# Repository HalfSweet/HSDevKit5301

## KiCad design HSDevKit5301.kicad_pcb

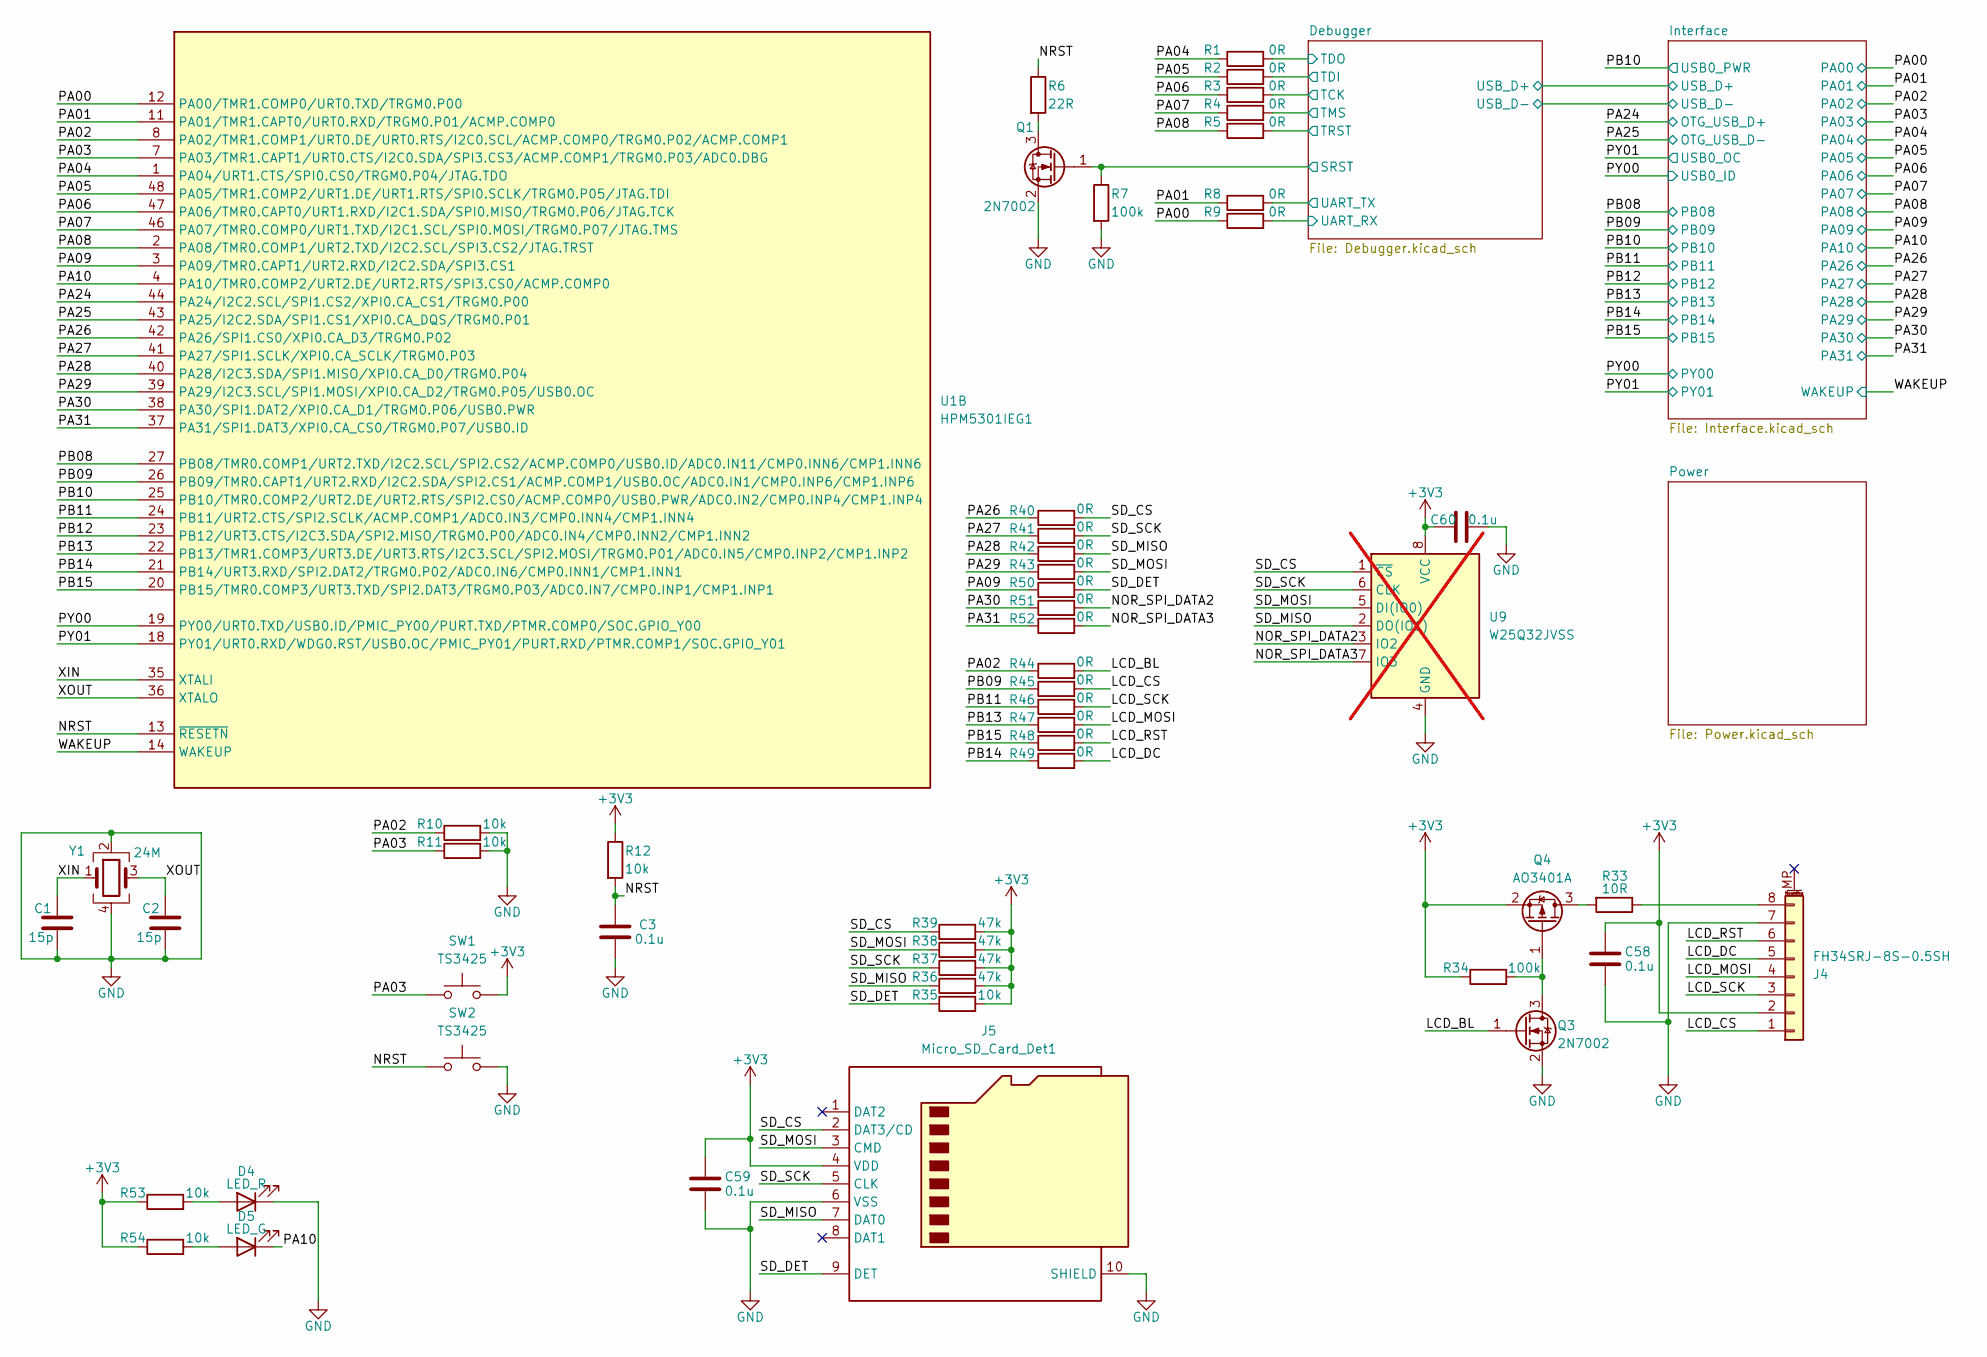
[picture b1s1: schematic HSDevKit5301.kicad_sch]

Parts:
C1, C2: 15p; C_0402_1005Metric
C3, C58, C59, C60: 0.1u; C_0402_1005Metric
D4: LED_R; LED_0402_1005Metric
D5: LED_G; LED_0402_1005Metric
J4: FH34SRJ-8S-0.5SH; FPC-SMD_8P-P0.50-FH34SRJ
J5: Micro_SD_Card_Det1; TF-SMD_TF-06A
Q1, Q3: 2N7002; SOT-323_SC-70
Q4: AO3401A; SOT-23
R1, R2, R3, R4, R5, R8, R9, R40, R41, R42, R43, R44, R45, R46, R47, R48, R49, R50, R51, R52: 0R; R_0402_1005Metric
R6: 22R; R_0402_1005Metric
R7, R34: 100k; R_0402_1005Metric
R10, R11, R12, R35, R53, R54: 10k; R_0402_1005Metric
R33: 10R; R_0603_1608Metric
R36, R37, R38, R39: 47k; R_0402_1005Metric
SW1, SW2: TS3425; SW_SPST_PTS810
U1: HPM5301IEG1; QFN-48-1EP_6x6mm_P0.4mm_EP4.2x4.2mm
U9: W25Q32JVSS; SOIC-8_5.23x5.23mm_P1.27mm; not fitted
Y1: 24M; Crystal_SMD_2016-4Pin_2.0x1.6mm

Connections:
+3V3: C58.1, C59.1, C60.1, J4.2, J5.4 (VDD), Q4.2 (S), R12.1, R34.1, R35.2, R36.2, R37.2, R38.2, R39.2, R53.1, R54.1, SW1.2, U9.8 (VCC); also elsewhere on the board
/Debugger/SRST: Q1.1 (G), R7.1; also elsewhere on the board
/Debugger/TCK: R3.2; also elsewhere on the board
/Debugger/TDI: R2.2; also elsewhere on the board
/Debugger/TDO: R1.2; also elsewhere on the board
/Debugger/TMS: R4.2; also elsewhere on the board
/Debugger/TRST: R5.2; also elsewhere on the board
/Debugger/UART_RX: R9.2; also elsewhere on the board
/Debugger/UART_TX: R8.2; also elsewhere on the board
/LCD_BL: Q3.1 (G), R44.2
/LCD_CS: J4.1, R45.2
/LCD_DC: J4.5, R49.2
/LCD_MOSI: J4.4, R47.2
/LCD_RST: J4.6, R48.2
/LCD_SCK: J4.3, R46.2
/NOR_SPI_DATA2: R51.2, U9.3 (IO2)
/NOR_SPI_DATA3: R52.2, U9.7 (IO3)
/NRST: C3.1, R6.1, R12.2, SW2.1, U1.13 (~RESETN)
/PA00: R9.1, U1.12 (PA00/TMR1.COMP0/URT0.TXD/TRGM0.P00); also elsewhere on the board
/PA01: R8.1, U1.11 (PA01/TMR1.CAPT0/URT0.RXD/TRGM0.P01/ACMP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); also elsewhere on the board
/PA02: R10.1, R44.1, U1.8 (PA02/TMR1.COMP1/URT0.DE/URT0.RTS/I2C0.S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); also elsewhere on the board
/PA03: R11.1, SW1.1, U1.7 (PA03/TMR1.CAPT1/URT0.CTS/I2C0.SDA/SPI3.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); also elsewhere on the board
/PA04: R1.1, U1.1 (PA04/URT1.CTS/SPI0.CS0/TRGM0.P04/JTAG.T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); also elsewhere on the board
/PA05: R2.1, U1.48 (PA05/TMR1.COMP2/URT1.DE/URT1.RTS/SPI0.S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); also elsewhere on the board
/PA06: R3.1, U1.47 (PA06/TMR0.CAPT0/URT1.RXD/I2C1.SDA/SPI0.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); also elsewhere on the board
/PA07: R4.1, U1.46 (PA07/TMR0.COMP0/URT1.TXD/I2C1.SCL/SPI0.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); also elsewhere on the board
/PA08: R5.1, U1.2 (PA08/TMR0.COMP1/URT2.TXD/I2C2.SCL/SPI3.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); also elsewhere on the board
/PA09: R50.1, U1.3 (PA09/TMR0.CAPT1/URT2.RXD/I2C2.SDA/SPI3.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); also elsewhere on the board
/PA10: D5.1 (K), U1.4 (PA10/TMR0.COMP2/URT2.DE/URT2.RTS/SPI3.C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); also elsewhere on the board
/PA24: U1.44 (PA24/I2C2.SCL/SPI1.CS2/XPI0.CA_CS1/TRGM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); also elsewhere on the board
/PA25: U1.43 (PA25/I2C2.SDA/SPI1.CS1/XPI0.CA_DQS/TRGM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); also elsewhere on the board
/PA26: R40.1, U1.42 (PA26/SPI1.CS0/XPI0.CA_D3/TRGM0.P02); also elsewhere on the board
/PA27: R41.1, U1.41 (PA27/SPI1.SCLK/XPI0.CA_SCLK/TRGM0.P03); also elsewhere on the board
/PA28: R42.1, U1.40 (PA28/I2C3.SDA/SPI1.MISO/XPI0.CA_D0/TRGM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); also elsewhere on the board
/PA29: R43.1, U1.39 (PA29/I2C3.SCL/SPI1.MOSI/XPI0.CA_D2/TRGM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); also elsewhere on the board
/PA30: R51.1, U1.38 (PA30/SPI1.DAT2/XPI0.CA_D1/TRGM0.P06/USB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); also elsewhere on the board
/PA31: R52.1, U1.37 (PA31/SPI1.DAT3/XPI0.CA_CS0/TRGM0.P07/US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); also elsewhere on the board
/PB08: U1.27 (PB08/TMR0.COMP1/URT2.TXD/I2C2.SCL/SPI2.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); also elsewhere on the board
/PB09: R45.1, U1.26 (PB09/TMR0.CAPT1/URT2.RXD/I2C2.SDA/SPI2.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); also elsewhere on the board
/PB10: U1.25 (PB10/TMR0.COMP2/URT2.DE/URT2.RTS/SPI2.C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); also elsewhere on the board
/PB11: R46.1, U1.24 (PB11/URT2.CTS/SPI2.SCLK/ACMP.COMP1/ADC0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); also elsewhere on the board
/PB12: U1.23 (PB12/URT3.CTS/I2C3.SDA/SPI2.MISO/TRGM0.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); also elsewhere on the board
/PB13: R47.1, U1.22 (PB13/TMR1.COMP3/URT3.DE/URT3.RTS/I2C3.S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); also elsewhere on the board
/PB14: R49.1, U1.21 (PB14/URT3.RXD/SPI2.DAT2/TRGM0.P02/ADC0.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); also elsewhere on the board
/PB15: R48.1, U1.20 (PB15/TMR0.COMP3/URT3.TXD/SPI2.DAT3/TRGM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); also elsewhere on the board
/PY00: U1.19 (PY00/URT0.TXD/USB0.ID/PMIC_PY00/PURT.TX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); also elsewhere on the board
/PY01: U1.18 (PY01/URT0.RXD/WDG0.RST/USB0.OC/PMIC_PY0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); also elsewhere on the board
/SD_CS: J5.2 (DAT3/CD), R39.1, R40.2, U9.1 (~CS)
/SD_DET: J5.9 (DET), R35.1, R50.2
/SD_MISO: J5.7 (DAT0), R36.1, R42.2, U9.2 (DO(IO1))
/SD_MOSI: J5.3 (CMD), R38.1, R43.2, U9.5 (DI(IO0))
/SD_SCK: J5.5 (CLK), R37.1, R41.2, U9.6 (CLK)
/WAKEUP: U1.14 (WAKEUP); also elsewhere on the board
/XIN: C1.1, U1.35 (XTALI), Y1.1
/XOUT: C2.1, U1.36 (XTALO), Y1.3
GND: C1.2, C2.2, C3.2, C58.2, C59.2, C60.2, D4.1 (K), J4.7, J5.6 (VSS), J5.10 (SHIELD), Q1.2 (S), Q3.2 (S), R7.2, R10.2, R11.2, SW2.2, U9.4 (GND), Y1.2, Y1.4; also elsewhere on the board
unnamed: D4.2 (A), R53.2
unnamed: D5.2 (A), R54.2
unnamed: J4.8, R33.1
unnamed: Q1.3 (D), R6.2
unnamed: Q3.3 (D), Q4.1 (G), R34.2
unnamed: Q4.3 (D), R33.2

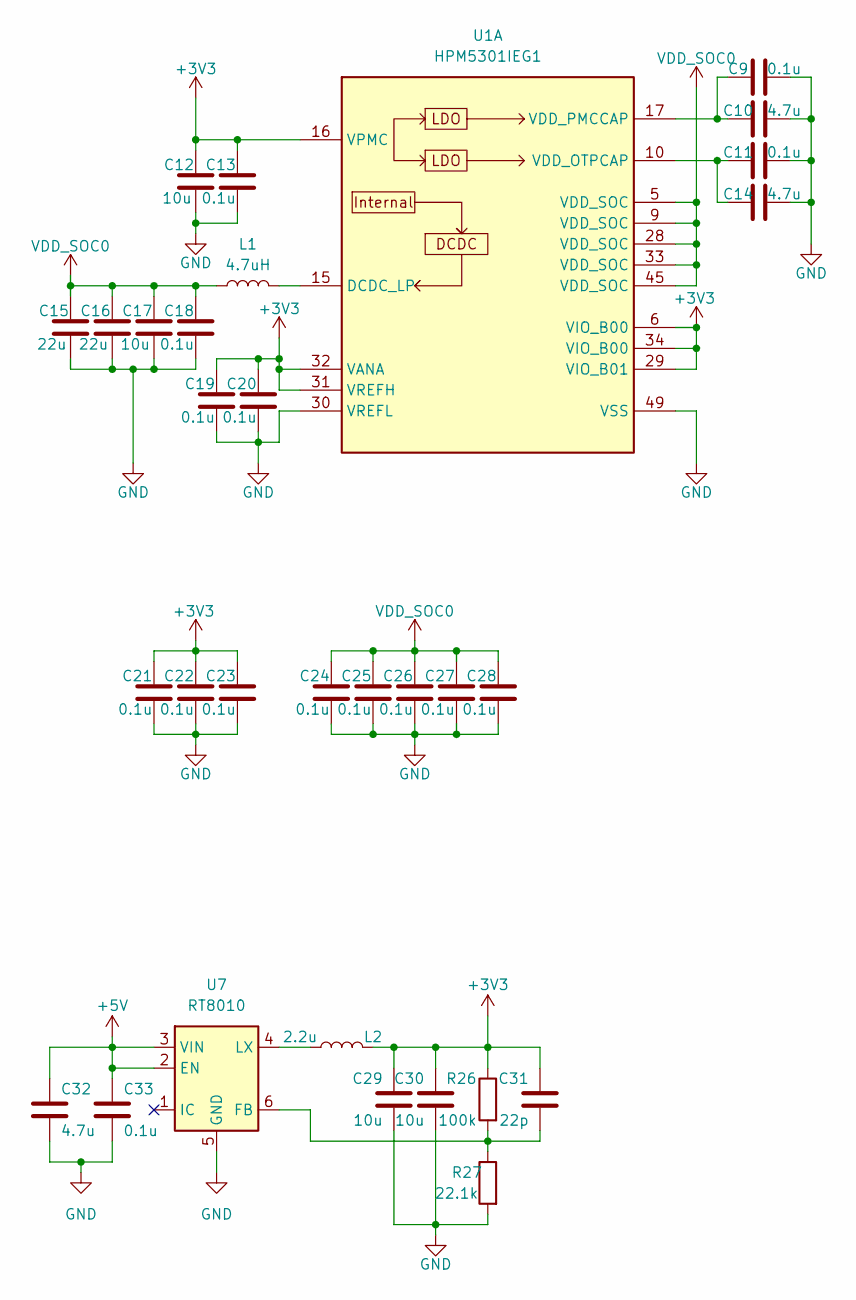
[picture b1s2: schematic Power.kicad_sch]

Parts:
C9, C11, C13, C18, C19, C20, C21, C22, C23, C24, C25, C26, C27, C28, C33: 0.1u; C_0402_1005Metric
C10, C14, C32: 4.7u; C_0402_1005Metric
C12, C17, C29, C30: 10u; C_0402_1005Metric
C15, C16: 22u; C_0402_1005Metric
C31: 22p; C_0402_1005Metric
L1: 4.7uH; L_1008_2520Metric
L2: 2.2u; L_1008_2520Metric
R26: 100k; R_0402_1005Metric
R27: 22.1k; R_0402_1005Metric
U1: HPM5301IEG1; QFN-48-1EP_6x6mm_P0.4mm_EP4.2x4.2mm
U7: RT8010; DFN-6-1EP_2x2mm_P0.65mm_EP1.01x1.7mm

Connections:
+3V3: C12.1, C13.1, C19.1, C20.1, C21.1, C22.1, C23.1, C29.1, C30.1, C31.1, L2.1, R26.1, U1.6 (VIO_B00), U1.16 (VPMC), U1.29 (VIO_B01), U1.31 (VREFH), U1.32 (VANA), U1.34 (VIO_B00); also elsewhere on the board
+5V: C32.1, C33.1, U7.2 (EN), U7.3 (VIN); also elsewhere on the board
GND: C9.2, C10.2, C11.2, C12.2, C13.2, C14.2, C15.2, C16.2, C17.2, C18.2, C19.2, C20.2, C21.2, C22.2, C23.2, C24.2, C25.2, C26.2, C27.2, C28.2, C29.2, C30.2, C32.2, C33.2, R27.2, U1.30 (VREFL), U1.49 (VSS), U7.5 (GND), U7.7 (GND); also elsewhere on the board
unnamed: L1.2, U1.15 (DCDC_LP)
unnamed: C11.1, C14.1, U1.10 (VDD_OTPCAP)
unnamed: C9.1, C10.1, U1.17 (VDD_PMCCAP)
unnamed: C31.2, R26.2, R27.1, U7.6 (FB)
unnamed: L2.2, U7.4 (LX)
VDD_SOC0: C15.1, C16.1, C17.1, C18.1, C24.1, C25.1, C26.1, C27.1, C28.1, L1.1, U1.5 (VDD_SOC), U1.9 (VDD_SOC), U1.28 (VDD_SOC), U1.33 (VDD_SOC), U1.45 (VDD_SOC)

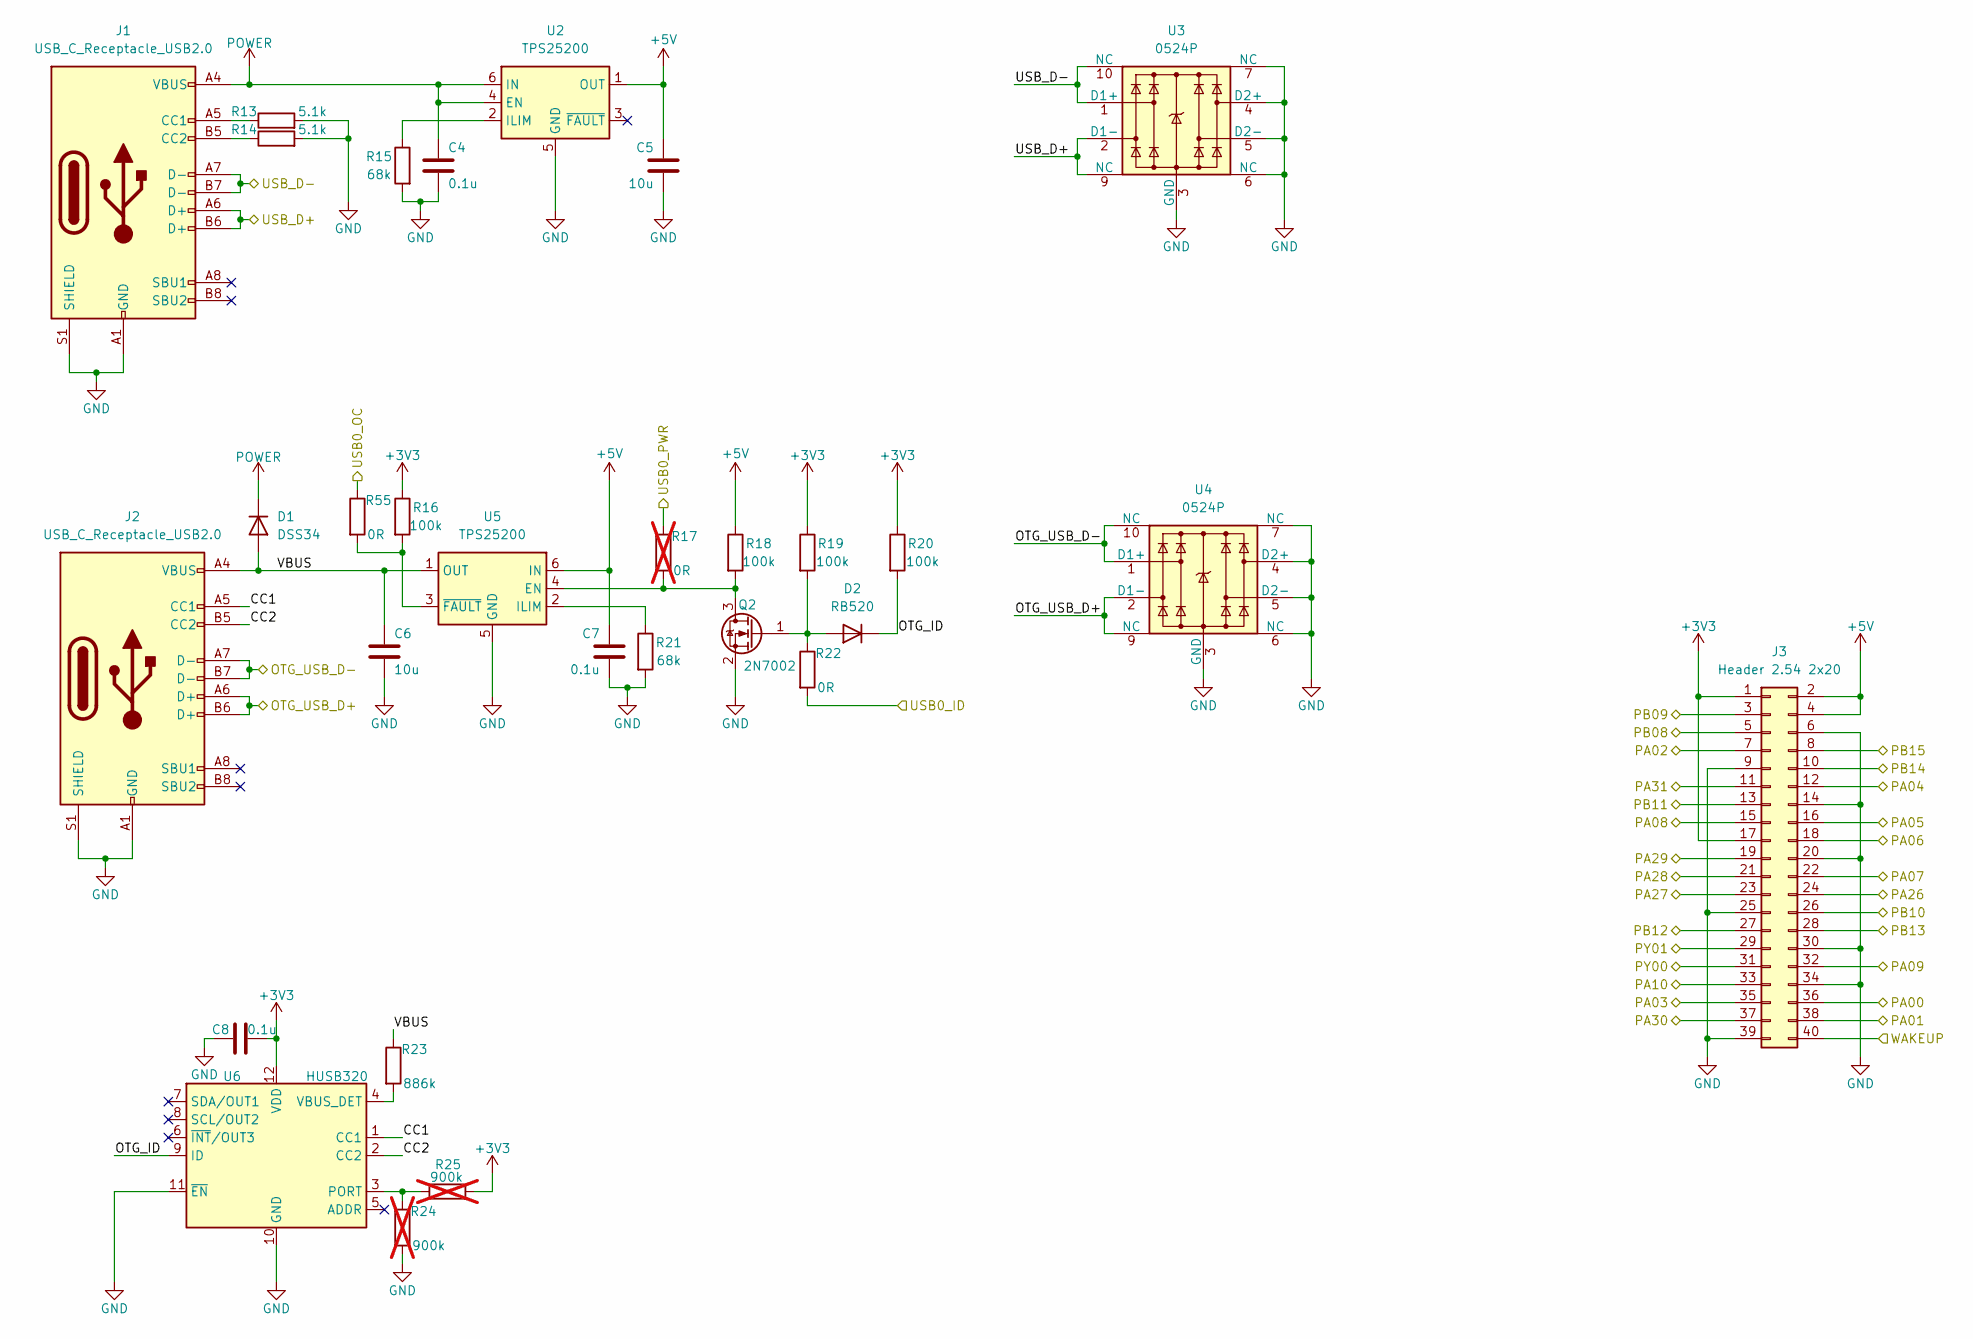
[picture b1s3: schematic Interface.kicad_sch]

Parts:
C4, C7, C8: 0.1u; C_0402_1005Metric
C5, C6: 10u; C_0402_1005Metric
D1: DSS34; D_SOD-123
D2: RB520; D_SOD-523
J1, J2: USB_C_Receptacle_USB2.0; USB-C-SMD_CX90M-16P
J3: Header 2.54 2x20; PinHeader_2x20_P2.54mm_Vertical
Q2: 2N7002; SOT-323_SC-70
R13, R14: 5.1k; R_0402_1005Metric
R15, R21: 68k; R_0402_1005Metric
R16, R18, R19, R20: 100k; R_0402_1005Metric
R17: 0R; R_0402_1005Metric; not fitted
R22, R55: 0R; R_0402_1005Metric
R23: 886k; R_0402_1005Metric
R24, R25: 900k; R_0402_1005Metric; not fitted
U2, U5: TPS25200; DFN-6-1EP_2x2mm_P0.65mm_EP1x1.6mm
U3, U4: 0524P; USON-10_2.5x1.0mm_P0.5mm
U6: HUSB320; Texas_X2QFN-12_1.6x1.6mm_P0.4mm

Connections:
+3V3: C8.2, J3.1, J3.17, R16.1, R19.1, R20.1, R25.2, U6.12 (VDD); also elsewhere on the board
+5V: C5.1, C7.1, J3.2, J3.4, R18.1, U2.1 (OUT), U5.6 (IN); also elsewhere on the board
/Interface/CC1: J2.A5 (CC1), U6.1 (CC1)
/Interface/CC2: J2.B5 (CC2), U6.2 (CC2)
/Interface/OTG_ID: D2.1 (K), R20.2, U6.9 (ID)
/Interface/USB_D+: J1.A6 (D+), J1.B6 (D+), U3.2 (D1-), U3.9 (NC); also elsewhere on the board
/Interface/USB_D-: J1.A7 (D-), J1.B7 (D-), U3.1 (D1+), U3.10 (NC); also elsewhere on the board
/Interface/VBUS: C6.1, D1.2 (A), J2.A4 (VBUS), J2.A9 (VBUS), J2.B4 (VBUS), J2.B9 (VBUS), R23.1, U5.1 (OUT)
/PA00: J3.36; also elsewhere on the board
/PA01: J3.38; also elsewhere on the board
/PA02: J3.7; also elsewhere on the board
/PA03: J3.35; also elsewhere on the board
/PA04: J3.12; also elsewhere on the board
/PA05: J3.16; also elsewhere on the board
/PA06: J3.18; also elsewhere on the board
/PA07: J3.22; also elsewhere on the board
/PA08: J3.15; also elsewhere on the board
/PA09: J3.32; also elsewhere on the board
/PA10: J3.33; also elsewhere on the board
/PA24: J2.A6 (D+), J2.B6 (D+), U4.2 (D1-), U4.9 (NC); also elsewhere on the board
/PA25: J2.A7 (D-), J2.B7 (D-), U4.1 (D1+), U4.10 (NC); also elsewhere on the board
/PA26: J3.24; also elsewhere on the board
/PA27: J3.23; also elsewhere on the board
/PA28: J3.21; also elsewhere on the board
/PA29: J3.19; also elsewhere on the board
/PA30: J3.37; also elsewhere on the board
/PA31: J3.11; also elsewhere on the board
/PB08: J3.5; also elsewhere on the board
/PB09: J3.3; also elsewhere on the board
/PB10: J3.26, R17.1; also elsewhere on the board
/PB11: J3.13; also elsewhere on the board
/PB12: J3.27; also elsewhere on the board
/PB13: J3.28; also elsewhere on the board
/PB14: J3.10; also elsewhere on the board
/PB15: J3.8; also elsewhere on the board
/PY00: J3.31, R22.2; also elsewhere on the board
/PY01: J3.29, R55.1; also elsewhere on the board
/WAKEUP: J3.40; also elsewhere on the board
GND: C4.2, C5.2, C6.2, C7.2, C8.1, J1.A1 (GND), J1.A12 (GND), J1.B1 (GND), J1.B12 (GND), J1.S1 (SHIELD), J2.A1 (GND), J2.A12 (GND), J2.B1 (GND), J2.B12 (GND), J2.S1 (SHIELD), J3.6, J3.9, J3.14, J3.20, J3.25, J3.30, J3.34, J3.39, Q2.2 (S), R13.2, R14.2, R15.2, R21.2, R24.2, U2.5 (GND), U2.7 (GND), U3.3 (GND), U3.4 (D2+), U3.5 (D2-), U3.6 (NC), U3.7 (NC), U3.8 (GND), U4.3 (GND), U4.4 (D2+), U4.5 (D2-), U4.6 (NC), U4.7 (NC), U4.8 (GND), U5.5 (GND), U5.7 (GND), U6.10 (GND), U6.11 (~EN); also elsewhere on the board
unnamed: D2.2 (A), Q2.1 (G), R19.2, R22.1
unnamed: J1.A5 (CC1), R13.1
unnamed: J1.B5 (CC2), R14.1
unnamed: Q2.3 (D), R17.2, R18.2, U5.4 (EN)
unnamed: R15.1, U2.2 (ILIM)
unnamed: R21.1, U5.2 (ILIM)
unnamed: R16.2, R55.2, U5.3 (~FAULT)
unnamed: R24.1, R25.1, U6.3 (PORT)
unnamed: R23.2, U6.4 (VBUS_DET)
POWER: C4.1, D1.1 (K), J1.A4 (VBUS), J1.A9 (VBUS), J1.B4 (VBUS), J1.B9 (VBUS), U2.4 (EN), U2.6 (IN)

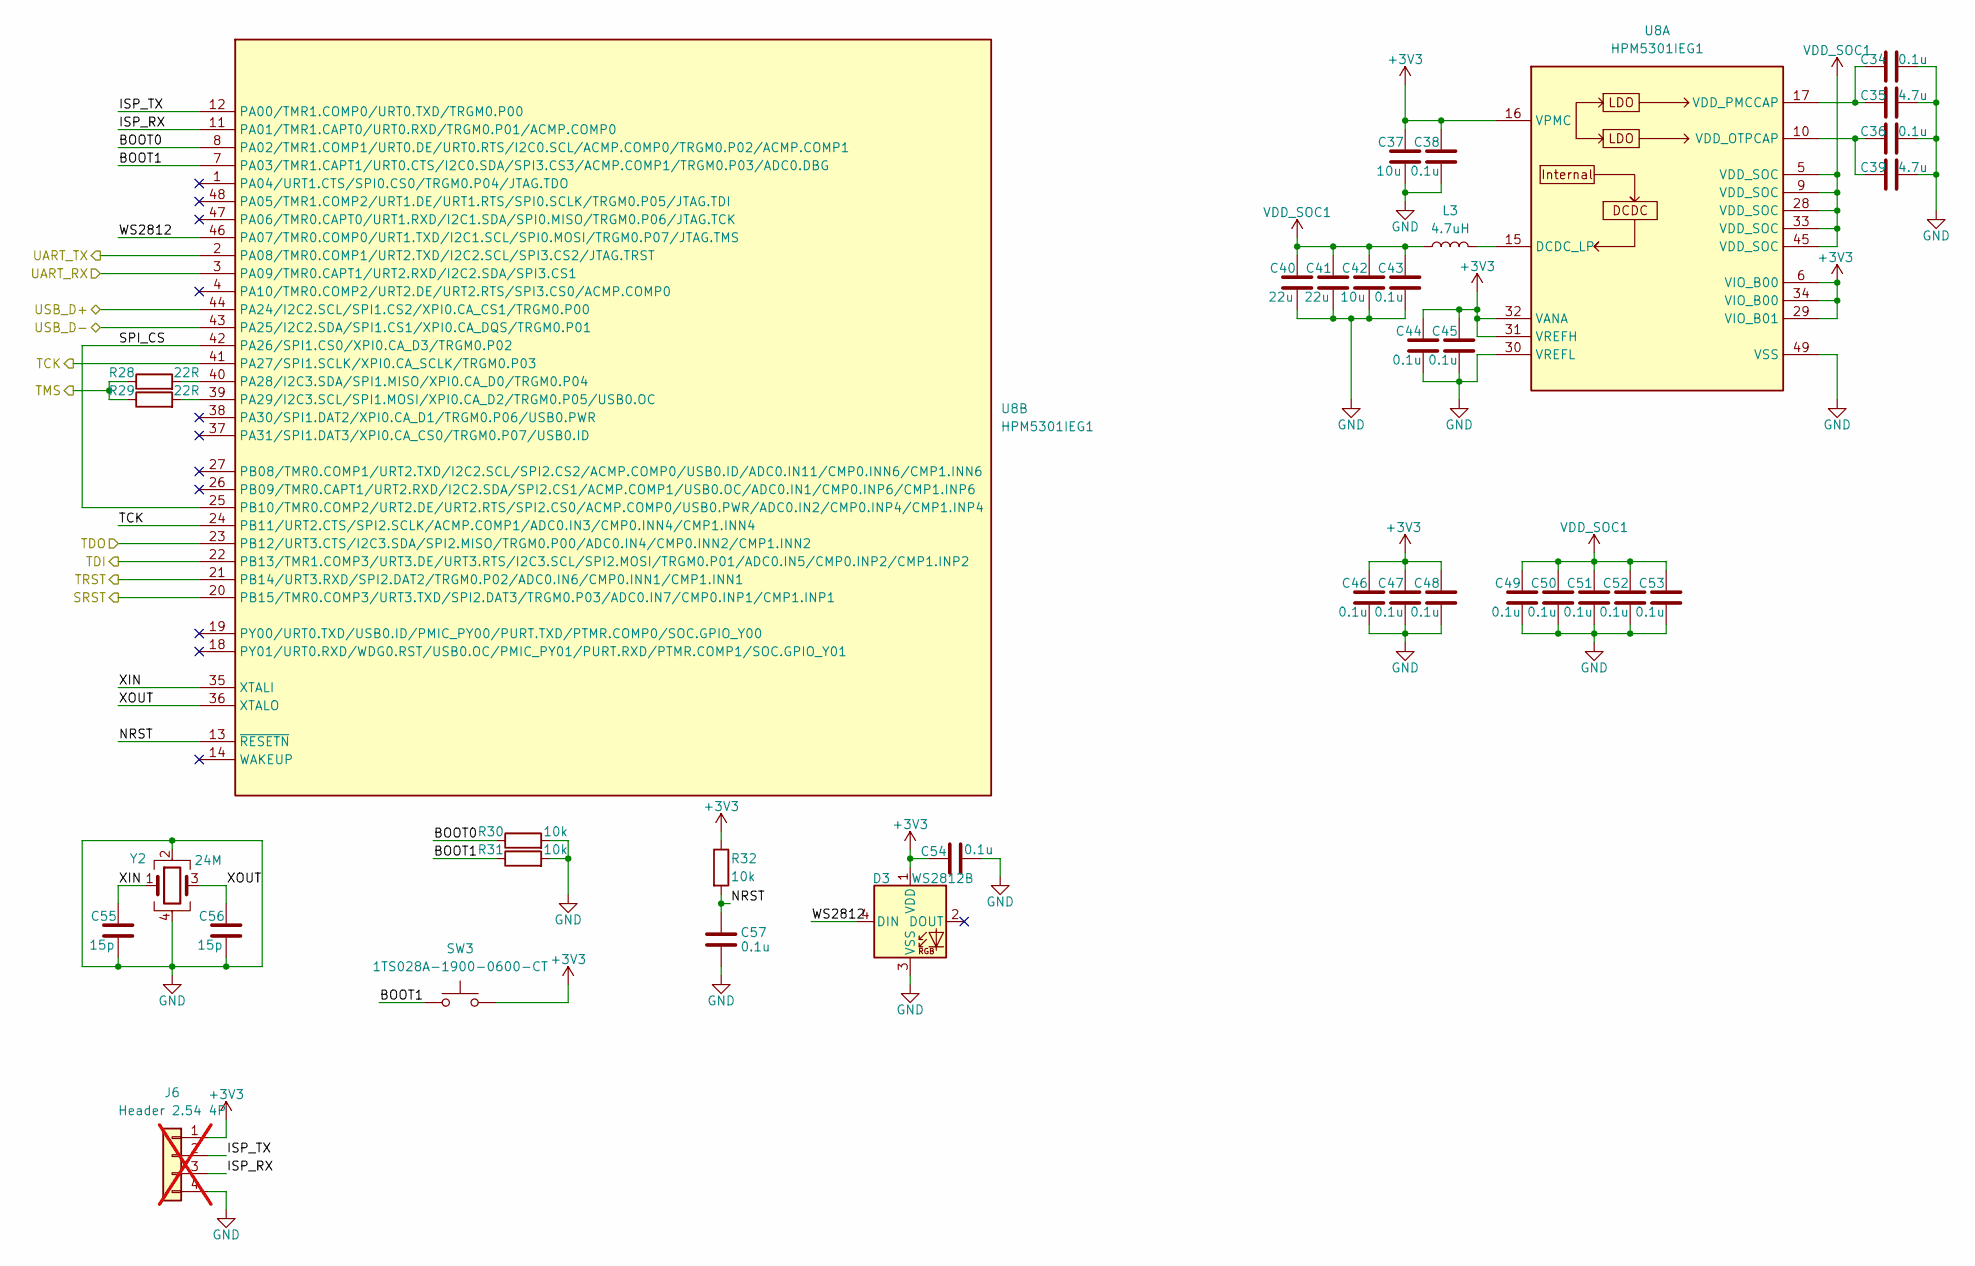
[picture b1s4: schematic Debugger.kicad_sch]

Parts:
C34, C36, C38, C43, C44, C45, C46, C47, C48, C49, C50, C51, C52, C53, C54, C57: 0.1u; C_0402_1005Metric
C35, C39: 4.7u; C_0402_1005Metric
C37, C42: 10u; C_0402_1005Metric
C40, C41: 22u; C_0402_1005Metric
C55, C56: 15p; C_0402_1005Metric
D3: WS2812B; LED_WS2812_0807
J6: Header 2.54 4P; PinHeader_1x04_P2.54mm_Vertical; not fitted
L3: 4.7uH; L_1008_2520Metric
R28, R29: 22R; R_0402_1005Metric
R30, R31, R32: 10k; R_0402_1005Metric
SW3: 1TS028A-1900-0600-CT; SW-SMD_4P-L2.8-W1.9-P1.20-LS3.0_1TS028A
U8: HPM5301IEG1; QFN-48-1EP_6x6mm_P0.4mm_EP4.2x4.2mm
Y2: 24M; Crystal_SMD_2016-4Pin_2.0x1.6mm

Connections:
+3V3: C37.1, C38.1, C44.1, C45.1, C46.1, C47.1, C48.1, C54.1, D3.1 (VDD), J6.1, R32.1, SW3.2, U8.6 (VIO_B00), U8.16 (VPMC), U8.29 (VIO_B01), U8.31 (VREFH), U8.32 (VANA), U8.34 (VIO_B00); also elsewhere on the board
/Debugger/BOOT0: R30.1, U8.8 (PA02/TMR1.COMP1/URT0.DE/URT0.RTS/I2C0.S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)
/Debugger/BOOT1: R31.1, SW3.1, U8.7 (PA03/TMR1.CAPT1/URT0.CTS/I2C0.SDA/SPI3.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)
/Debugger/ISP_RX: J6.3, U8.11 (PA01/TMR1.CAPT0/URT0.RXD/TRGM0.P01/ACMP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)
/Debugger/ISP_TX: J6.2, U8.12 (PA00/TMR1.COMP0/URT0.TXD/TRGM0.P00)
/Debugger/NRST: C57.1, R32.2, U8.13 (~RESETN)
/Debugger/SPI_CS: U8.25 (PB10/TMR0.COMP2/URT2.DE/URT2.RTS/SPI2.C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), U8.42 (PA26/SPI1.CS0/XPI0.CA_D3/TRGM0.P02)
/Debugger/SRST: U8.20 (PB15/TMR0.COMP3/URT3.TXD/SPI2.DAT3/TRGM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); also elsewhere on the board
/Debugger/TCK: U8.24 (PB11/URT2.CTS/SPI2.SCLK/ACMP.COMP1/ADC0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), U8.41 (PA27/SPI1.SCLK/XPI0.CA_SCLK/TRGM0.P03); also elsewhere on the board
/Debugger/TDI: U8.22 (PB13/TMR1.COMP3/URT3.DE/URT3.RTS/I2C3.S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); also elsewhere on the board
/Debugger/TDO: U8.23 (PB12/URT3.CTS/I2C3.SDA/SPI2.MISO/TRGM0.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); also elsewhere on the board
/Debugger/TMS: R28.1, R29.1; also elsewhere on the board
/Debugger/TRST: U8.21 (PB14/URT3.RXD/SPI2.DAT2/TRGM0.P02/ADC0.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); also elsewhere on the board
/Debugger/UART_RX: U8.3 (PA09/TMR0.CAPT1/URT2.RXD/I2C2.SDA/SPI3.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); also elsewhere on the board
/Debugger/UART_TX: U8.2 (PA08/TMR0.COMP1/URT2.TXD/I2C2.SCL/SPI3.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); also elsewhere on the board
/Debugger/WS2812: D3.4 (DIN), U8.46 (PA07/TMR0.COMP0/URT1.TXD/I2C1.SCL/SPI0.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)
/Debugger/XIN: C55.1, U8.35 (XTALI), Y2.1
/Debugger/XOUT: C56.1, U8.36 (XTALO), Y2.3
/Interface/USB_D+: U8.44 (PA24/I2C2.SCL/SPI1.CS2/XPI0.CA_CS1/TRGM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); also elsewhere on the board
/Interface/USB_D-: U8.43 (PA25/I2C2.SDA/SPI1.CS1/XPI0.CA_DQS/TRGM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); also elsewhere on the board
GND: C34.2, C35.2, C36.2, C37.2, C38.2, C39.2, C40.2, C41.2, C42.2, C43.2, C44.2, C45.2, C46.2, C47.2, C48.2, C49.2, C50.2, C51.2, C52.2, C53.2, C54.2, C55.2, C56.2, C57.2, D3.3 (VSS), J6.4, R30.2, R31.2, U8.30 (VREFL), U8.49 (VSS), Y2.2, Y2.4; also elsewhere on the board
unnamed: L3.2, U8.15 (DCDC_LP)
unnamed: C36.1, C39.1, U8.10 (VDD_OTPCAP)
unnamed: C34.1, C35.1, U8.17 (VDD_PMCCAP)
unnamed: R28.2, U8.40 (PA28/I2C3.SDA/SPI1.MISO/XPI0.CA_D0/TRGM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)
unnamed: R29.2, U8.39 (PA29/I2C3.SCL/SPI1.MOSI/XPI0.CA_D2/TRGM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)
VDD_SOC1: C40.1, C41.1, C42.1, C43.1, C49.1, C50.1, C51.1, C52.1, C53.1, L3.1, U8.5 (VDD_SOC), U8.9 (VDD_SOC), U8.28 (VDD_SOC), U8.33 (VDD_SOC), U8.45 (VDD_SOC)

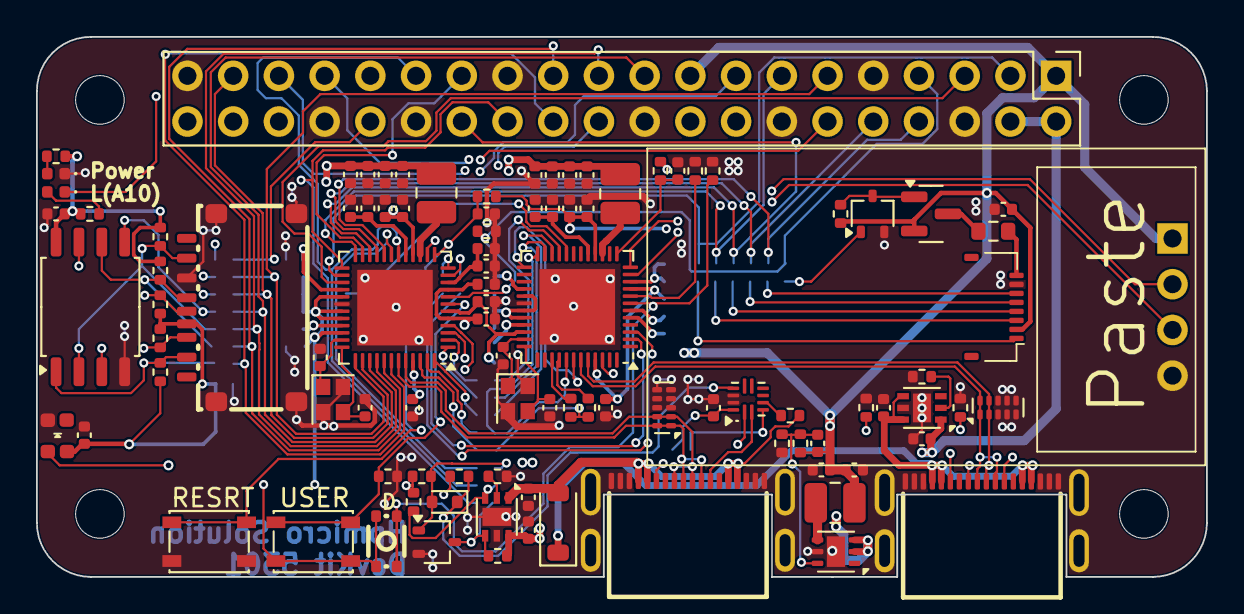
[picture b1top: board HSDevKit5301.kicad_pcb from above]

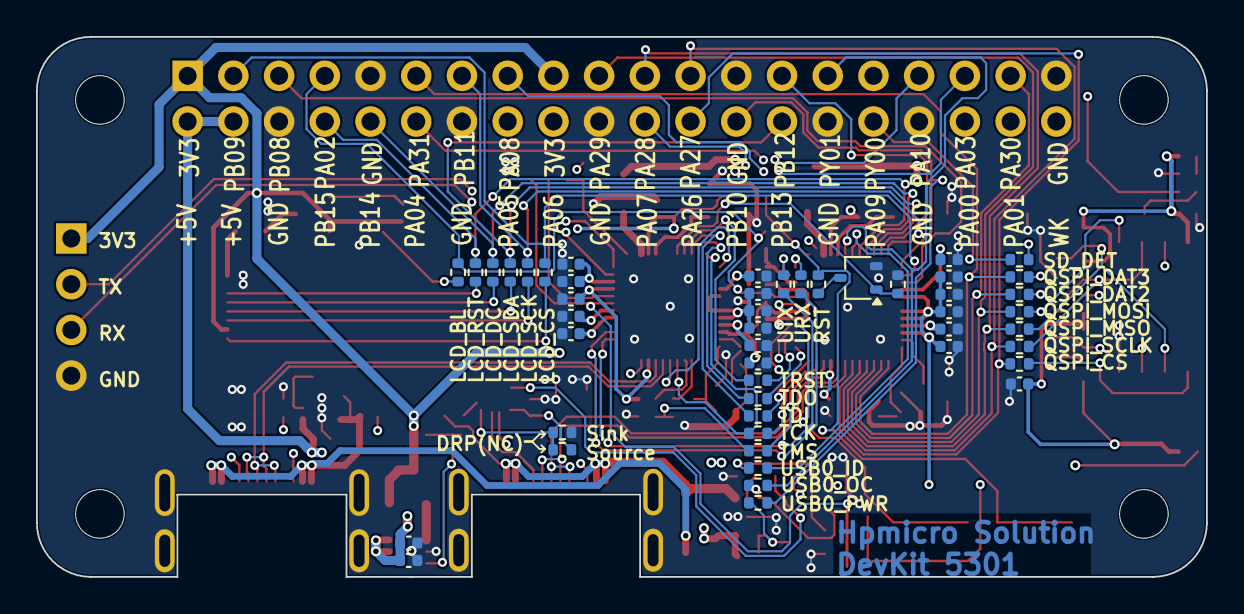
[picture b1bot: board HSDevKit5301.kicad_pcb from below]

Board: 4 copper layers, 65.0 x 30.0 mm, 151 parts (48 on the bottom side), 100 nets.

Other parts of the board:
MH1, MH2, MH3, MH4: MountingHole_2.7mm_M2.5

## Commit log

2024-09-16 add: 添加原理图
2024-09-21 update: 更新PCB
